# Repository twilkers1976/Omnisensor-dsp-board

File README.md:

# omnisensorv2
kicad 10.03 schematic and pcb project
#omni_cpu_board

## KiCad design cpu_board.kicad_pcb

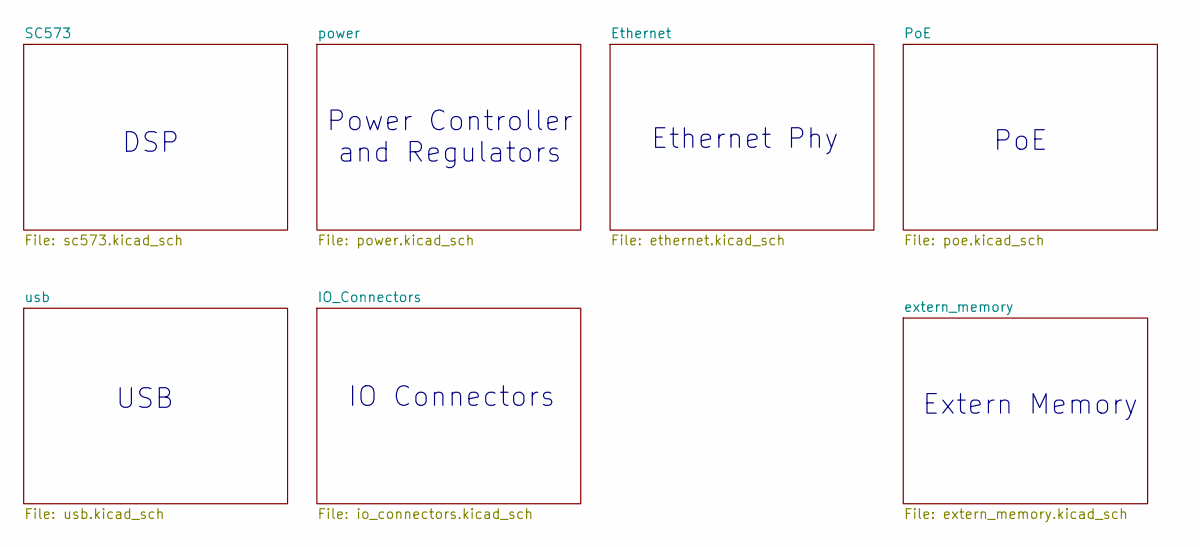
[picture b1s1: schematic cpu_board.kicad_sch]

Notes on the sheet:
PoE
Extern Memory
IO Connectors
Ethernet Phy
Power Controller and Regulators
DSP
USB

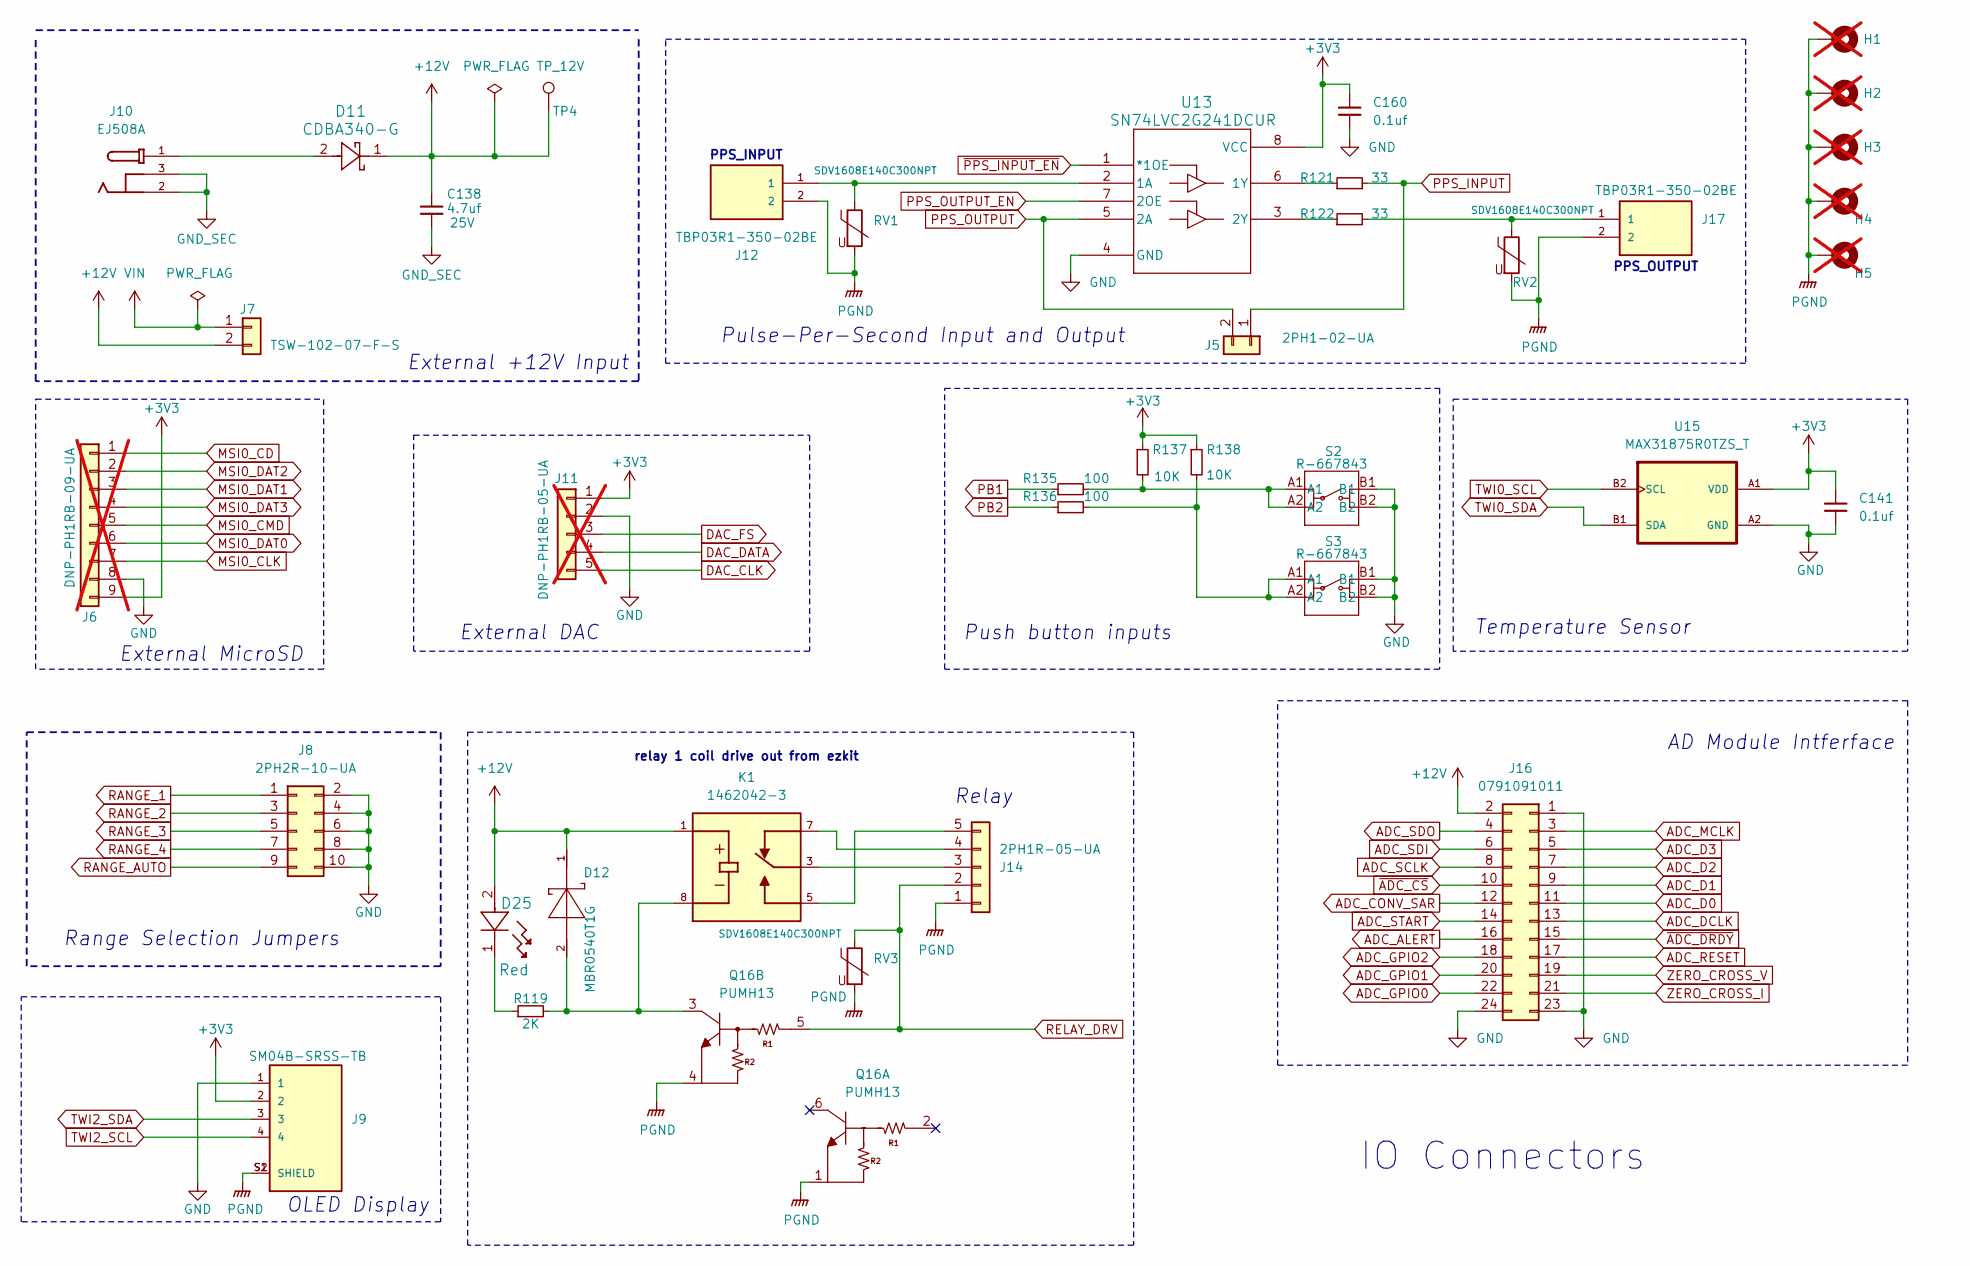
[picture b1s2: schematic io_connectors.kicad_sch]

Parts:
C138: 4.7uf; C_1210_3225Metric; Voltage 25V; Rating 25V; Part Number C1210C475K3RACTU
C141, C160: 0.1uf; C_0402_1005Metric; Rating 50V; Part Number 04025C104KAT2A
D11: CDBA340-G; CDBA-G; Part Number CDBA340-G
D12: MBR0540T1G; SOD-123; Part Number MBR0540T1G
D25: Red; LED_B1931NG_HVK; Part Number B1911USD-20D000114U1930
H1, H2, H3, H4, H5: MountingHole; MountingHole_2.5mm_Pad_TopBottom; not fitted
J5: 2PH1-02-UA; PinHeader_1x02_P2.00mm_Vertical; Part Number 2PH1-02-UA
J6: DNP-PH1RB-09-UA; PinHeader_1x09_P2.54mm_Vertical; Part Number PH1RB-09-UA; not fitted
J7: TSW-102-07-F-S; PinHeader_1x02_P2.54mm_Vertical; Rating 3A; Part Number TSW-102-07-F-S
J8: 2PH2R-10-UA; PinHeader_2x05_P2.00mm_Vertical; Part Number 2PH2R-10-UA
J9: SM04B-SRSS-TB; JST_SM04B-SRSS-TB(LF)(SN); Part Number SM04B-SRSS-TB
J10: EJ508A; MPD_EJ508A; PARTREV J
J11: DNP-PH1RB-05-UA; PinHeader_1x05_P2.54mm_Vertical; Part Number PH1RB-05-UA; not fitted
J12, J17: TBP03R1-350-02BE; CUI_TBP03R1-350-02BE; Part Number TBP03R1-350-02BE
J14: 2PH1R-05-UA; PinHeader_1x05_P2.00mm_Vertical; Part Number 2PH1R-05-UA
J16: 0791091011; PinSocket_2x12_P2.00mm_Vertical_SMD; Part Number 0791091011
K1: 1462042-3; PARTREV 0721
Q16: PUMH13; SOP65P210X110-6N; Part Numnber PUMH13F; DIGIKEY MUN5114T1GOSCT-ND
R119: 2K; R_0603_1608Metric; Rating 1/10 W; Part Number RN73H1JTTD2001F100
R121, R122: 33; R_0402_1005Metric; Part Number RMCF0402FT33R0
R135, R136: 100; R_0402_1005Metric; Part Number RMCF0402FT100R
R137, R138: 10K; R_0402_1005Metric; Part Number RMCF0402FT10K0
RV1, RV2, RV3: SDV1608E140C300NPT; R_0603_1608Metric; Part Number SDV1608E140C300NPT
S2, S3: R-667843; R-667843_MIT; PARTREV 14 Apr 22
TP4: TP_12V; TestPoint_Pad_D1.0mm
U13: SN74LVC2G241DCUR; DCU8; Part Number SN74LVC2G241DCUR
U15: MAX31875R0TZS_T; BGA4N40P2X2_83X83X37N; Part Number MAX31875R0TZS+T

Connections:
+3V3: C141.1, C160.1, J6.9, J9.2, J11.1, R137.1, R138.1, U13.8 (VCC), U15.A1 (VDD); also elsewhere on the board
+12V: C138.1, D11.1, D12.1, D25.2, J7.2, J16.2, K1.1, TP4.1 (1_1); also elsewhere on the board
ADC_ALERT: J16.16; also elsewhere on the board
ADC_CONV_SAR: J16.12; also elsewhere on the board
ADC_D0: J16.11; also elsewhere on the board
ADC_D1: J16.9; also elsewhere on the board
ADC_D2: J16.7; also elsewhere on the board
ADC_D3: J16.5; also elsewhere on the board
ADC_DCLK: J16.13; also elsewhere on the board
ADC_GPIO0: J16.22; also elsewhere on the board
ADC_GPIO1: J16.20; also elsewhere on the board
ADC_GPIO2: J16.18; also elsewhere on the board
ADC_MCLK: J16.3; also elsewhere on the board
ADC_RESET: J16.17; also elsewhere on the board
ADC_SCLK: J16.8; also elsewhere on the board
ADC_SDI: J16.6; also elsewhere on the board
ADC_SDO: J16.4; also elsewhere on the board
ADC_START: J16.14; also elsewhere on the board
DAC_CLK: J11.5; also elsewhere on the board
DAC_DATA: J11.4; also elsewhere on the board
DAC_FS: J11.3; also elsewhere on the board
GND: C141.2, C160.2, J6.8, J8.2, J8.4, J8.6, J8.8, J8.10, J9.1, J11.2, J16.1, J16.23, J16.24, S2.B1, S2.B2, S3.B1, S3.B2, U13.4 (GND), U15.A2 (GND); also elsewhere on the board
GND_SEC: C138.2, J10.2, J10.3; also elsewhere on the board
MSI0_CD: J6.1; also elsewhere on the board
MSI0_CLK: J6.7; also elsewhere on the board
MSI0_CMD: J6.5; also elsewhere on the board
MSI0_DAT0: J6.6; also elsewhere on the board
MSI0_DAT1: J6.3; also elsewhere on the board
MSI0_DAT2: J6.2; also elsewhere on the board
MSI0_DAT3: J6.4; also elsewhere on the board
unnamed: D11.2, J10.1
unnamed: D25.1, R119.1
unnamed: J14.3, K1.3
unnamed: J14.4, K1.7
unnamed: J14.5, K1.5
unnamed: J17.1, R122.2, RV2.1
unnamed: D12.2, K1.8, Q16.3 (COLLECTOR), R119.2
unnamed: R135.2, R137.2, S2.A1, S2.A2
unnamed: R136.2, R138.2, S3.A1, S3.A2
unnamed: J12.1, RV1.1, U13.2 (1A)
unnamed: R121.1, U13.6 (1Y)
unnamed: R122.1, U13.3 (2Y)
PB1: R135.1; also elsewhere on the board
PB2: R136.1; also elsewhere on the board
PGND: H1.1 (1_1), H2.1 (1_1), H3.1 (1_1), H4.1 (1_1), H5.1 (1_1), J9.S1 (SHIELD), J9.S2 (SHIELD), J12.2, J14.1, J17.2, Q16.1 (EMITTER), Q16.4 (EMITTER), RV1.2, RV2.2, RV3.2; also elsewhere on the board
PPS_INPUT: J5.1, R121.2; also elsewhere on the board
PPS_OUTPUT: J5.2, U13.5 (2A); also elsewhere on the board
PPS_OUTPUT_EN: U13.7 (2OE); also elsewhere on the board
RANGE_1: J8.1; also elsewhere on the board
RANGE_2: J8.3; also elsewhere on the board
RANGE_3: J8.5; also elsewhere on the board
RANGE_4: J8.7; also elsewhere on the board
RANGE_AUTO: J8.9; also elsewhere on the board
RELAY_DRV: J14.2, Q16.5 (BASE), RV3.1; also elsewhere on the board
TWI0_SCL: U15.B2 (SCL); also elsewhere on the board
TWI0_SDA: U15.B1 (SDA); also elsewhere on the board
TWI2_SCL: J9.4; also elsewhere on the board
TWI2_SDA: J9.3; also elsewhere on the board
VIN: J7.1; also elsewhere on the board
ZERO_CROSS_I: J16.21; also elsewhere on the board
ZERO_CROSS_V: J16.19; also elsewhere on the board
~ADC_CS: J16.10; also elsewhere on the board
~ADC_DRDY: J16.15; also elsewhere on the board
~PPS_INPUT_EN: U13.1 (*1OE); also elsewhere on the board

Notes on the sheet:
Range Selection Jumpers
relay 1 coil drive out from ezkit
External MicroSD
Push button inputs
IO Connectors
Pulse-Per-Second Input and Output
PPS_OUTPUT
PPS_INPUT
AD Module Intferface
External +12V Input
Temperature Sensor
OLED Display
Relay
External DAC

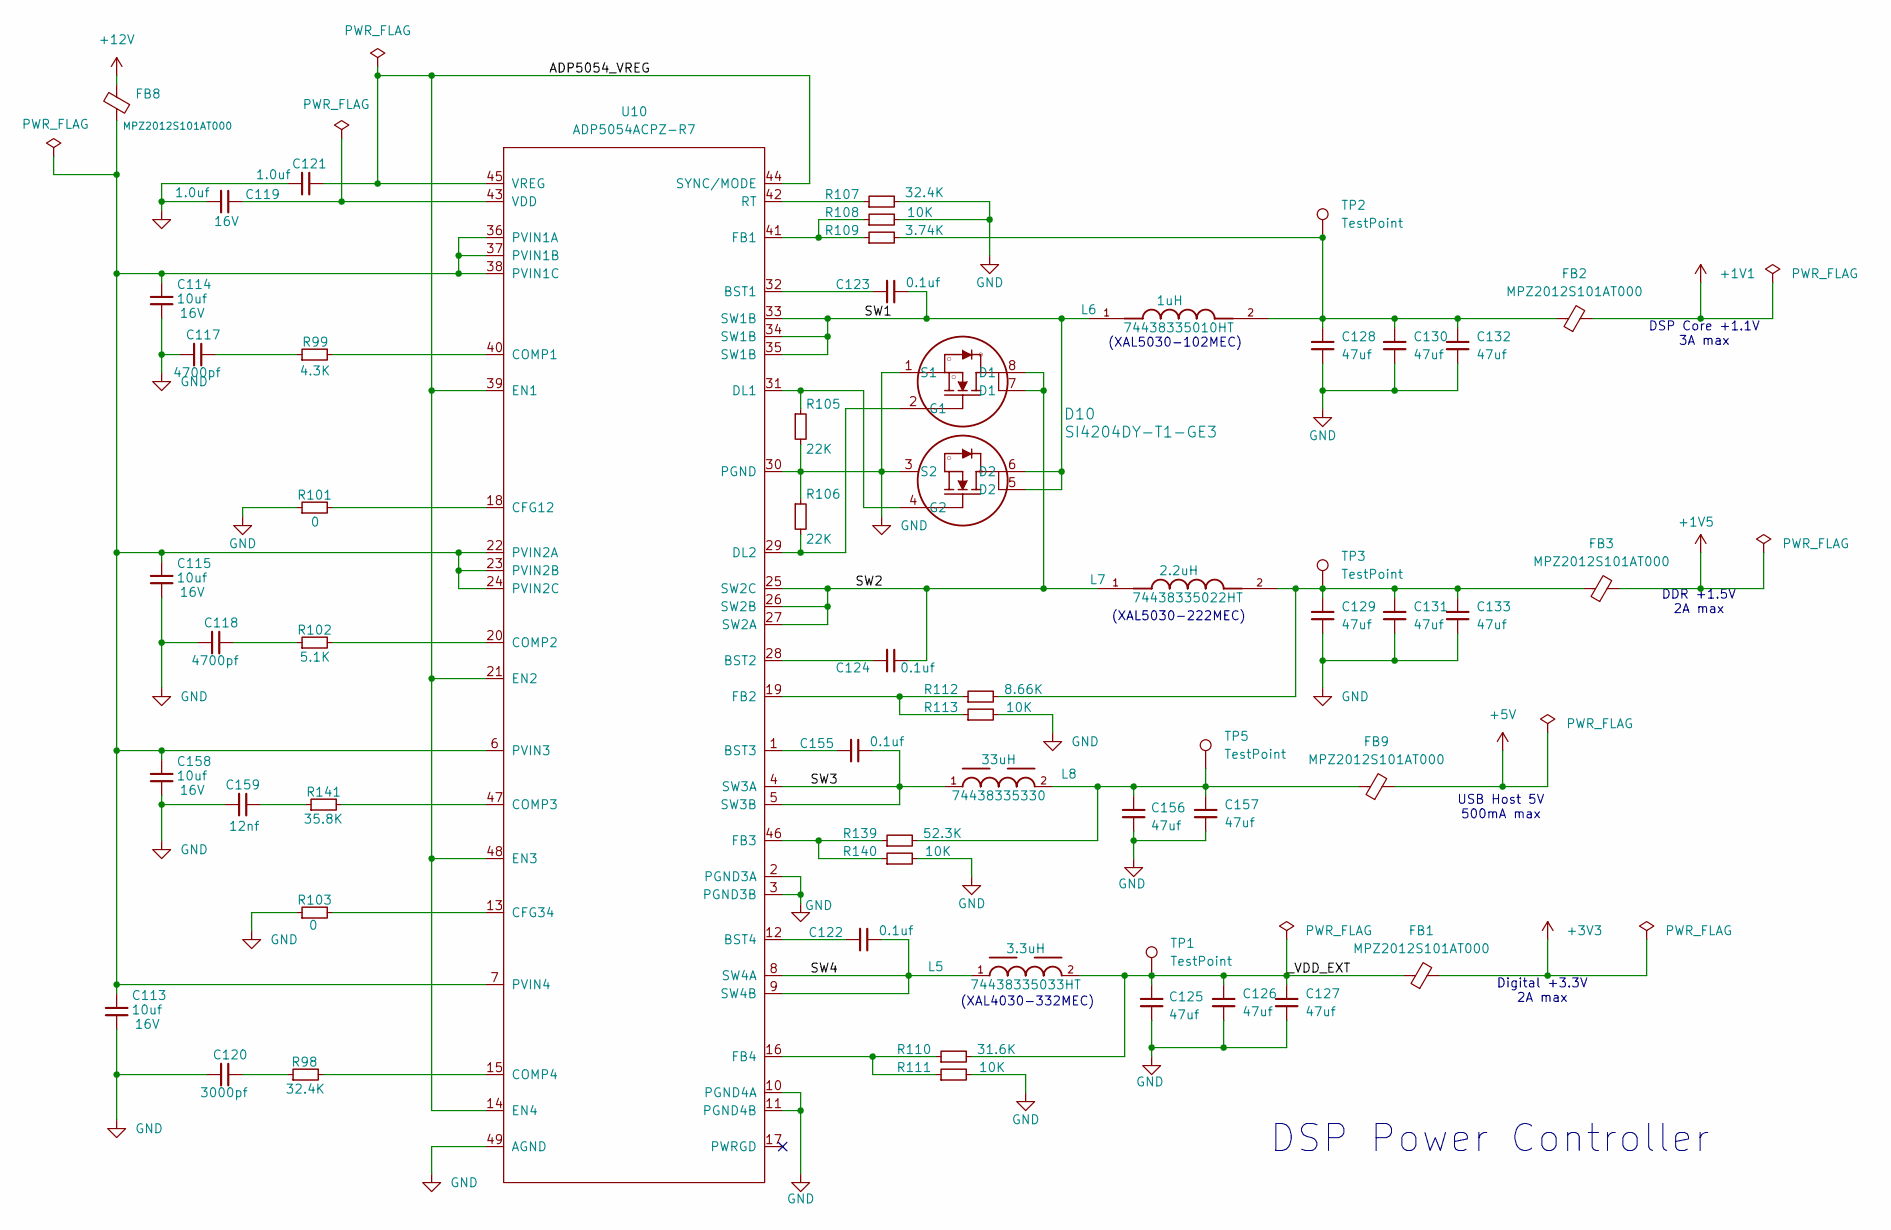
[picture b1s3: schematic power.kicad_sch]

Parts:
C113, C114, C115, C158: 10uf; C_0805_2012Metric; Voltage 16V; Rating 16V; Part Number EMK212BJ106KG-T
C117, C118: 4700pf; C_0402_1005Metric; Rating 50V; Part Number GCM155R71H472KA37D
C119, C121: 1.0uf; C_0402_1005Metric; Voltage 16V; Rating 16V; Part Number EMK105BJ105KV-F
C120: 3000pf; C_0402_1005Metric; Rating 50V; Part Number GMC04X7R302K50NT
C122, C123, C124, C155: 0.1uf; C_0402_1005Metric; Rating 50V; Part Number 04025C104KAT2A
C125, C126, C127, C128, C129, C130, C131, C132, C133, C156, C157: 47uf; C_0805_2012Metric; Rating 6.3V; Part Number JMK212BJ476MG-T
C159: 12nf; C_0402_1005Metric; Rating 50V; Part Number GCM155R71H122KA37D
D10: SI4204DY-T1-GE3; SOIC8_MS-012_VIS; Part Number SI4204DY-T1-GE3
FB1, FB3, FB8, FB9: MPZ2012S101AT000; L_0805_2012Metric; Rating 4A, 100 ohm; Part Number MPZ2012S101AT000
FB2: MPZ2012S101AT000; L_0805_2012Metric; Rating 4A, 100ohm; Part Number MPZ2012S101AT000
L5: 3.3uH; WE-MAPI_3015; Rating 2.7A; Part Number 74438335033HT
L6: 1uH; WE-MAPI_3015; Rating 4.5A; Part Number 74438335010HT
L7: 2.2uH; WE-MAPI_3015; Rating 3.2A; Part Number 74438335022HT
L8: 33uH; WE-MAPI_3015; Rating 500mA; Part Number 74438335330
R98, R107: 32.4K; R_0402_1005Metric; Part Number RMCF0402FT32K4
R99: 4.3K; R_0402_1005Metric; Part Number RMCF0402FT4K30
R101, R103: 0; R_0402_1005Metric; Part Number RMCF0402ZT0R00
R102: 5.1K; R_0402_1005Metric; Part Number RMCF0402FT5K10
R105, R106: 22K; R_0402_1005Metric; Part Number RMCF0402FT22K0
R108, R111, R113, R140: 10K; R_0402_1005Metric; Part Number RMCF0402FT10K0
R109: 3.74K; R_0402_1005Metric; Part Number RMCF0402FT3K74
R110: 31.6K; R_0402_1005Metric; Part Number RMCF0402FT31K6
R112: 8.66K; R_0402_1005Metric; Part Number RMCF0402FT8K66
R139: 52.3K; R_0402_1005Metric; Part Number RMCF0402FT52K3
R141: 35.8K; R_0402_1005Metric; Part Number RMCF0402FT35K7
TP1, TP2, TP3, TP5: TestPoint; TestPoint_Pad_D1.0mm
U10: ADP5054ACPZ-R7; CP_48_13_ADI; Part Number ADP5054ACPZ-R7

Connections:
+1V1: FB2.2; also elsewhere on the board
+1V5: FB3.2; also elsewhere on the board
+3V3: FB1.2; also elsewhere on the board
+5V: FB9.2; also elsewhere on the board
+12V: FB8.2; also elsewhere on the board
/power/ADP5054_VREG: C121.1, U10.14 (EN4), U10.21 (EN2), U10.39 (EN1), U10.44 (SYNC/MODE), U10.45 (VREG), U10.48 (EN3)
/power/SW1: C123.2, D10.5 (D2), D10.6 (D2), L6.1, U10.33 (SW1B), U10.34 (SW1B), U10.35 (SW1B)
/power/SW2: C124.2, D10.7 (D1), D10.8 (D1), L7.1, U10.25 (SW2C), U10.26 (SW2B), U10.27 (SW2A)
/power/SW3: C155.2, L8.1, U10.4 (SW3A), U10.5 (SW3B)
/power/SW4: C122.2, L5.1, U10.8 (SW4A), U10.9 (SW4B)
/power/_VDD_EXT: C125.1, C126.1, C127.1, FB1.1, L5.2, R110.2, TP1.1 (1_1)
GND: C113.2, C114.2, C115.2, C117.2, C118.2, C119.2, C120.2, C121.2, C125.2, C126.2, C127.2, C128.2, C129.2, C130.2, C131.2, C132.2, C133.2, C156.2, C157.2, C158.2, C159.2, D10.1 (S1), D10.3 (S2), R101.1, R103.1, R105.2, R106.1, R107.2, R108.2, R111.2, R113.2, R140.2, U10.2 (PGND3A), U10.3 (PGND3B), U10.10 (PGND4A), U10.11 (PGND4B), U10.30 (PGND), U10.49 (AGND); also elsewhere on the board
unnamed: C117.1, R99.1
unnamed: C118.1, R102.1
unnamed: C120.1, R98.1
unnamed: C128.1, C130.1, C132.1, FB2.1, L6.2, R109.2, TP2.1 (1_1)
unnamed: C129.1, C131.1, C133.1, FB3.1, L7.2, R112.2, TP3.1 (1_1)
unnamed: C156.1, C157.1, FB9.1, L8.2, R139.2, TP5.1 (1_1)
unnamed: C159.1, R141.1
unnamed: D10.2 (G1), R106.2, U10.29 (DL2)
unnamed: D10.4 (G2), R105.1, U10.31 (DL1)
unnamed: C123.1, U10.32 (BST1)
unnamed: C124.1, U10.28 (BST2)
unnamed: C155.1, U10.1 (BST3)
unnamed: C122.1, U10.12 (BST4)
unnamed: R101.2, U10.18 (CFG12)
unnamed: R103.2, U10.13 (CFG34)
unnamed: R99.2, U10.40 (COMP1)
unnamed: R102.2, U10.20 (COMP2)
unnamed: R141.2, U10.47 (COMP3)
unnamed: R98.2, U10.15 (COMP4)
unnamed: R108.1, R109.1, U10.41 (FB1)
unnamed: R112.1, R113.1, U10.19 (FB2)
unnamed: R139.1, R140.1, U10.46 (FB3)
unnamed: R110.1, R111.1, U10.16 (FB4)
unnamed: C113.1, C114.1, C115.1, C158.1, FB8.1, U10.6 (PVIN3), U10.7 (PVIN4), U10.22 (PVIN2A), U10.23 (PVIN2B), U10.24 (PVIN2C), U10.36 (PVIN1A), U10.37 (PVIN1B), U10.38 (PVIN1C)
unnamed: R107.1, U10.42 (RT)
unnamed: C119.1, U10.43 (VDD)

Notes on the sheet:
(XAL5030-222MEC)
(XAL5030-102MEC)
DDR +1.5V 2A max
Digital +3.3V 2A max
USB Host 5V 500mA max
DSP Core +1.1V 3A max
DSP Power Controller
(XAL4030-332MEC)

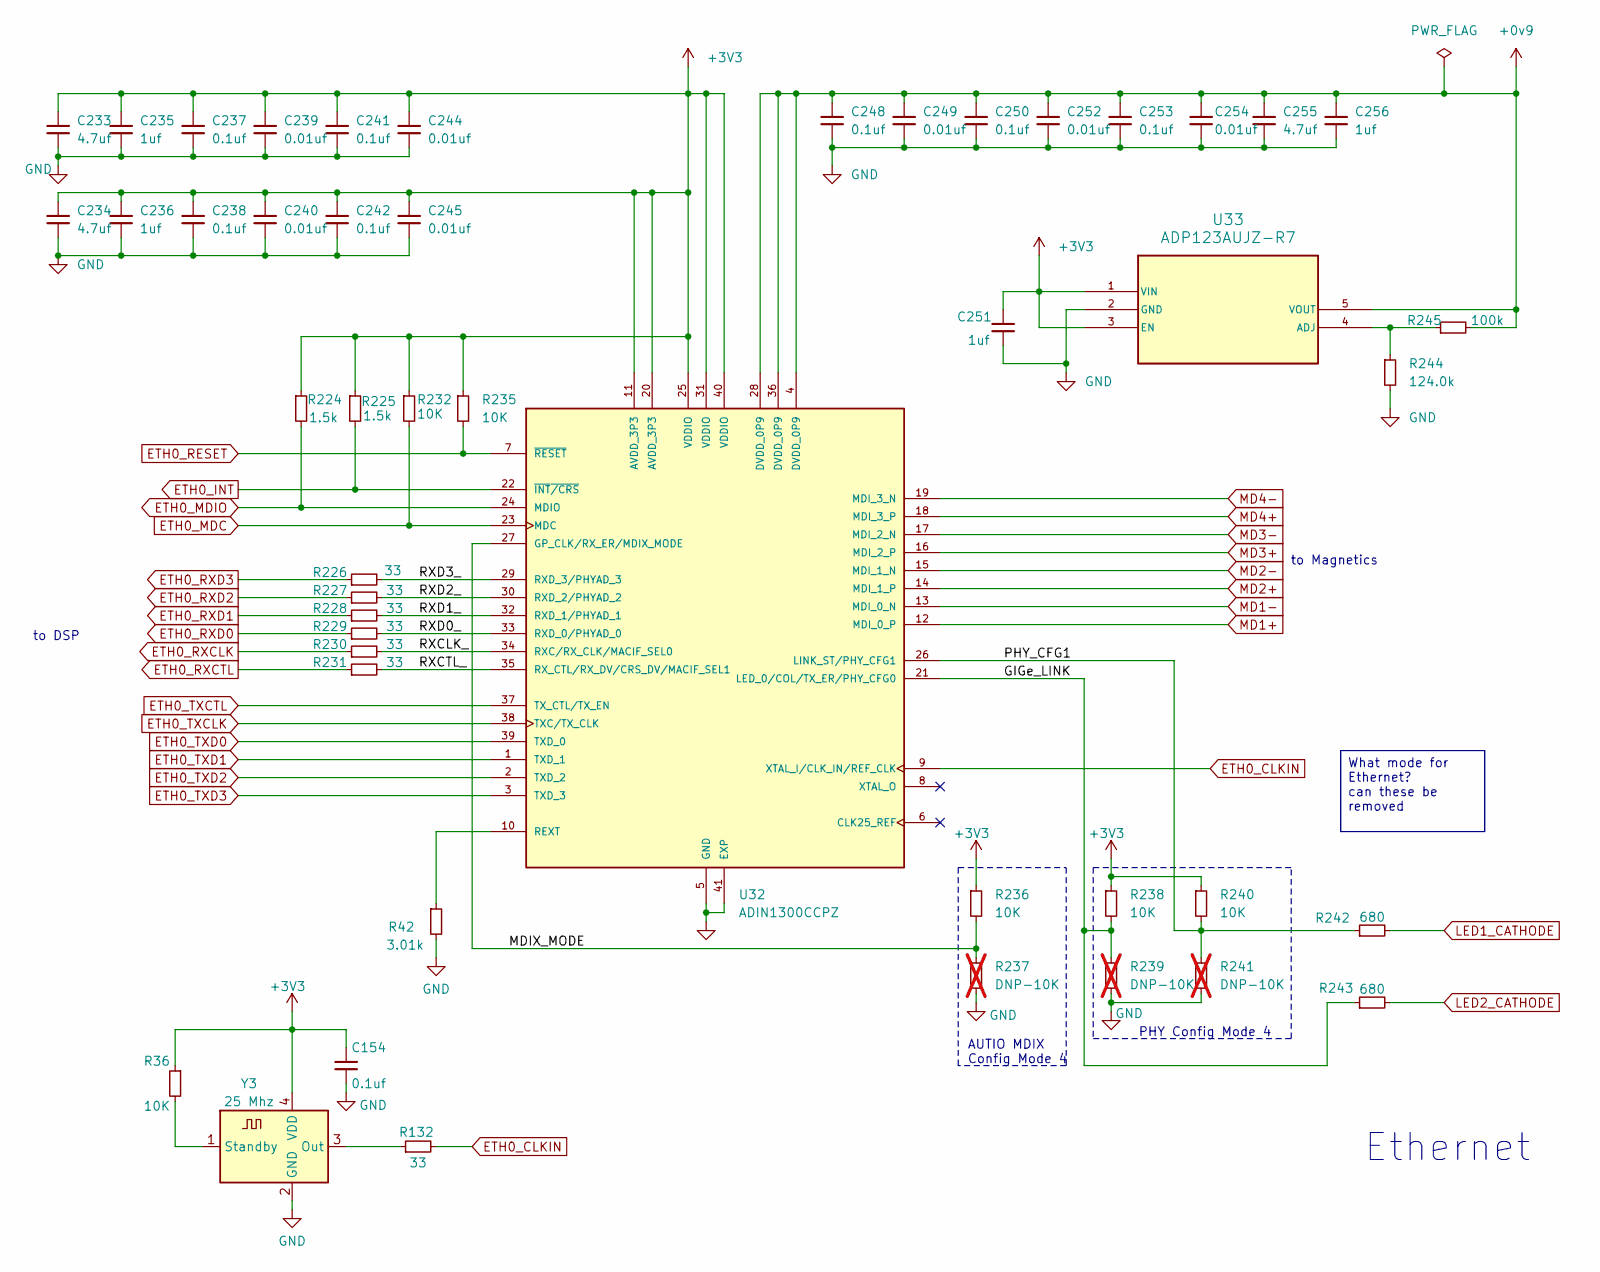
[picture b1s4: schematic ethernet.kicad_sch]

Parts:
C154, C237, C238, C241, C242, C248, C250, C253: 0.1uf; C_0402_1005Metric; Rating 50V; Part Number 04025C104KAT2A
C233, C234, C255: 4.7uf; C_0805_2012Metric; Rating 50V; Part Number CL21A475KBQNNNE
C235, C236, C251, C256: 1uf; C_0603_1608Metric; Rating 50V; Part Number 06035C105KAT2A
C239, C240, C244, C245, C249, C252, C254: 0.01uf; C_0402_1005Metric; Rating 50V; Part Number 04025C103KAT2A
R36, R232, R235, R236, R238, R240: 10K; R_0402_1005Metric; Part Number RMCF0402FT10K0
R42: 3.01k; R_0402_1005Metric; Part Number RMCF0402FT3K01
R132, R226, R227, R228, R229, R230, R231: 33; R_0402_1005Metric; Part Number RMCF0402FT33R0
R224, R225: 1.5k; R_0402_1005Metric; Part Number RMCF0402FT1K50
R237, R239, R241: DNP-10K; R_0402_1005Metric; Part Number RMCF0402FT10K0; not fitted
R242, R243: 680; R_0402_1005Metric; Part Number RMCF0402FT680R
R244: 124.0k; R_0402_1005Metric; Part Number RMCF0402FT124K
R245: 100k; R_0402_1005Metric; Part Number RMCF0402FT100K
U32: ADIN1300CCPZ; QFN50P600X600X80-41N; PARTREV 0
U33: ADP123AUJZ-R7; UJ-5_ADI; Part Number ADP123AUJZ-R7
Y3: 25 Mhz; OSC_4SMD_2.5MM_2.0MM; Part Number ECS-2520S33-250-FN-TR

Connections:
+0v9: C248.1, C249.1, C250.1, C252.1, C253.1, C254.1, C255.1, C256.1, R245.2, U32.4 (DVDD_0P9), U32.28 (DVDD_0P9), U32.36 (DVDD_0P9), U33.5 (VOUT)
+3V3: C154.1, C233.1, C234.1, C235.1, C236.1, C237.1, C238.1, C239.1, C240.1, C241.1, C242.1, C244.1, C245.1, C251.1, R36.1, R224.1, R225.1, R232.1, R235.1, R236.1, R238.1, R240.1, U32.11 (AVDD_3P3), U32.20 (AVDD_3P3), U32.25 (VDDIO), U32.31 (VDDIO), U32.40 (VDDIO), U33.1 (VIN), U33.3 (EN), Y3.4 (VDD); also elsewhere on the board
/Ethernet/GIGe_LINK: R238.2, R239.1, R243.1, U32.21 (LED_0/COL/TX_ER/PHY_CFG0)
/Ethernet/MDIX_MODE: R236.2, R237.1, U32.27 (GP_CLK/RX_ER/MDIX_MODE)
/Ethernet/PHY_CFG1: R240.2, R241.1, R242.1, U32.26 (LINK_ST/PHY_CFG1)
/Ethernet/RXCLK_: R230.2, U32.34 (RXC/RX_CLK/MACIF_SEL0)
/Ethernet/RXCTL_: R231.2, U32.35 (RX_CTL/RX_DV/CRS_DV/MACIF_SEL1)
/Ethernet/RXD0_: R229.2, U32.33 (RXD_0/PHYAD_0)
/Ethernet/RXD1_: R228.2, U32.32 (RXD_1/PHYAD_1)
/Ethernet/RXD2_: R227.2, U32.30 (RXD_2/PHYAD_2)
/Ethernet/RXD3_: R226.2, U32.29 (RXD_3/PHYAD_3)
ETH0_CLKIN: R132.2, U32.9 (XTAL_I/CLK_IN/REF_CLK); also elsewhere on the board
ETH0_INT: R225.2, U32.22 (~INT~/CRS); also elsewhere on the board
ETH0_MDC: R232.2, U32.23 (MDC); also elsewhere on the board
ETH0_MDIO: R224.2, U32.24 (MDIO); also elsewhere on the board
ETH0_RESET: R235.2, U32.7 (~RESET); also elsewhere on the board
ETH0_RXCLK: R230.1; also elsewhere on the board
ETH0_RXCTL: R231.1; also elsewhere on the board
ETH0_RXD0: R229.1; also elsewhere on the board
ETH0_RXD1: R228.1; also elsewhere on the board
ETH0_RXD2: R227.1; also elsewhere on the board
ETH0_RXD3: R226.1; also elsewhere on the board
ETH0_TXCLK: U32.38 (TXC/TX_CLK); also elsewhere on the board
ETH0_TXCTL: U32.37 (TX_CTL/TX_EN); also elsewhere on the board
ETH0_TXD0: U32.39 (TXD_0); also elsewhere on the board
ETH0_TXD1: U32.1 (TXD_1); also elsewhere on the board
ETH0_TXD2: U32.2 (TXD_2); also elsewhere on the board
ETH0_TXD3: U32.3 (TXD_3); also elsewhere on the board
GND: C154.2, C233.2, C234.2, C235.2, C236.2, C237.2, C238.2, C239.2, C240.2, C241.2, C242.2, C244.2, C245.2, C248.2, C249.2, C250.2, C251.2, C252.2, C253.2, C254.2, C255.2, C256.2, R42.2, R237.2, R239.2, R241.2, R244.2, U32.5 (GND), U32.41 (EXP), U33.2 (GND), Y3.2 (GND); also elsewhere on the board
LED1_CATHODE: R242.2; also elsewhere on the board
LED2_CATHODE: R243.2; also elsewhere on the board
MD1+: U32.12 (MDI_0_P); also elsewhere on the board
MD1-: U32.13 (MDI_0_N); also elsewhere on the board
MD2+: U32.14 (MDI_1_P); also elsewhere on the board
MD2-: U32.15 (MDI_1_N); also elsewhere on the board
MD3+: U32.16 (MDI_2_P); also elsewhere on the board
MD3-: U32.17 (MDI_2_N); also elsewhere on the board
MD4+: U32.18 (MDI_3_P); also elsewhere on the board
MD4-: U32.19 (MDI_3_N); also elsewhere on the board
unnamed: R42.1, U32.10 (REXT)
unnamed: R244.1, R245.1, U33.4 (ADJ)
unnamed: R132.1, Y3.3 (Out)
unnamed: R36.2, Y3.1 (Standby)

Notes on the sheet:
to Magnetics
to DSP
PHY Config Mode 4
Ethernet
AUTIO MDIX Config Mode 4
What mode for Ethernet? can these be removed

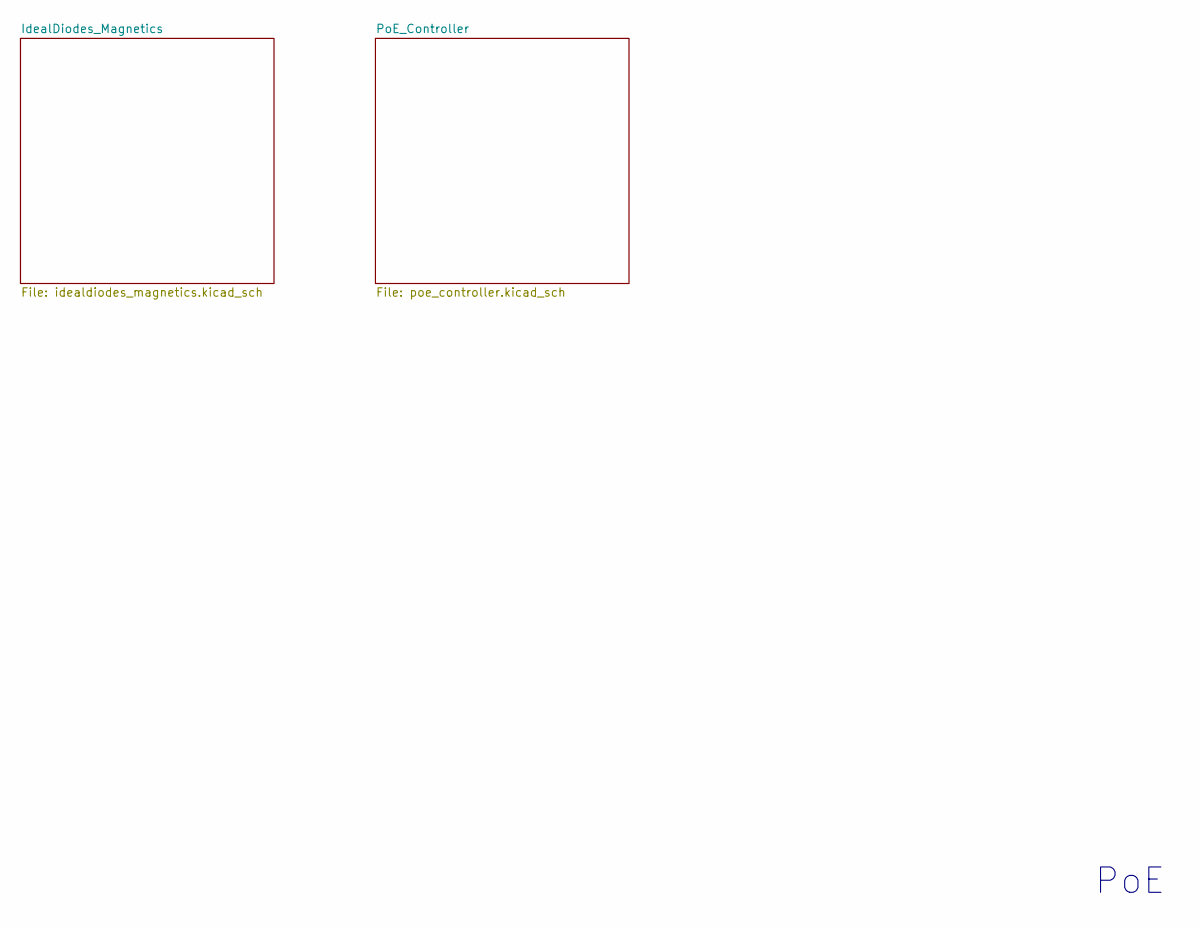
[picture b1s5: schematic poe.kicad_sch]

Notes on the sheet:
PoE

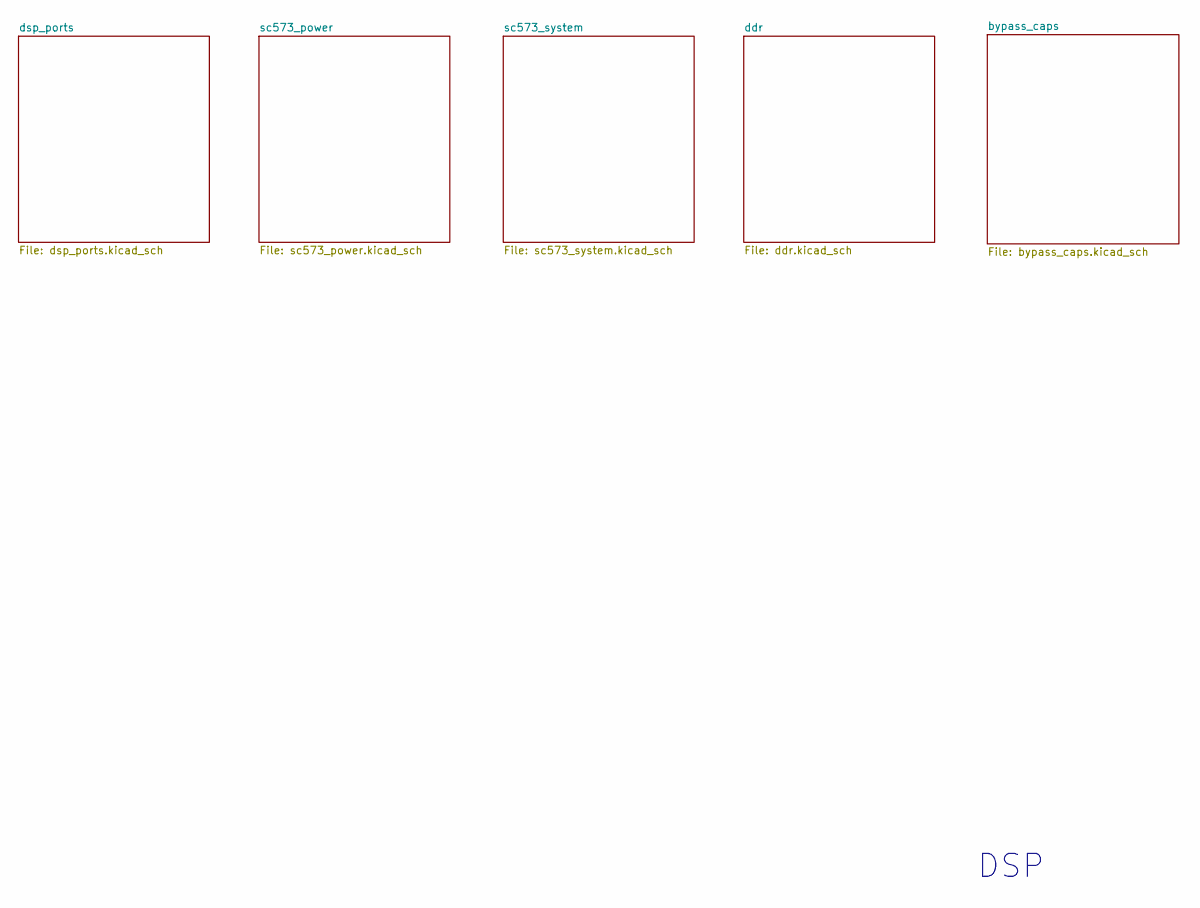
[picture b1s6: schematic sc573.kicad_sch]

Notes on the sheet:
DSP

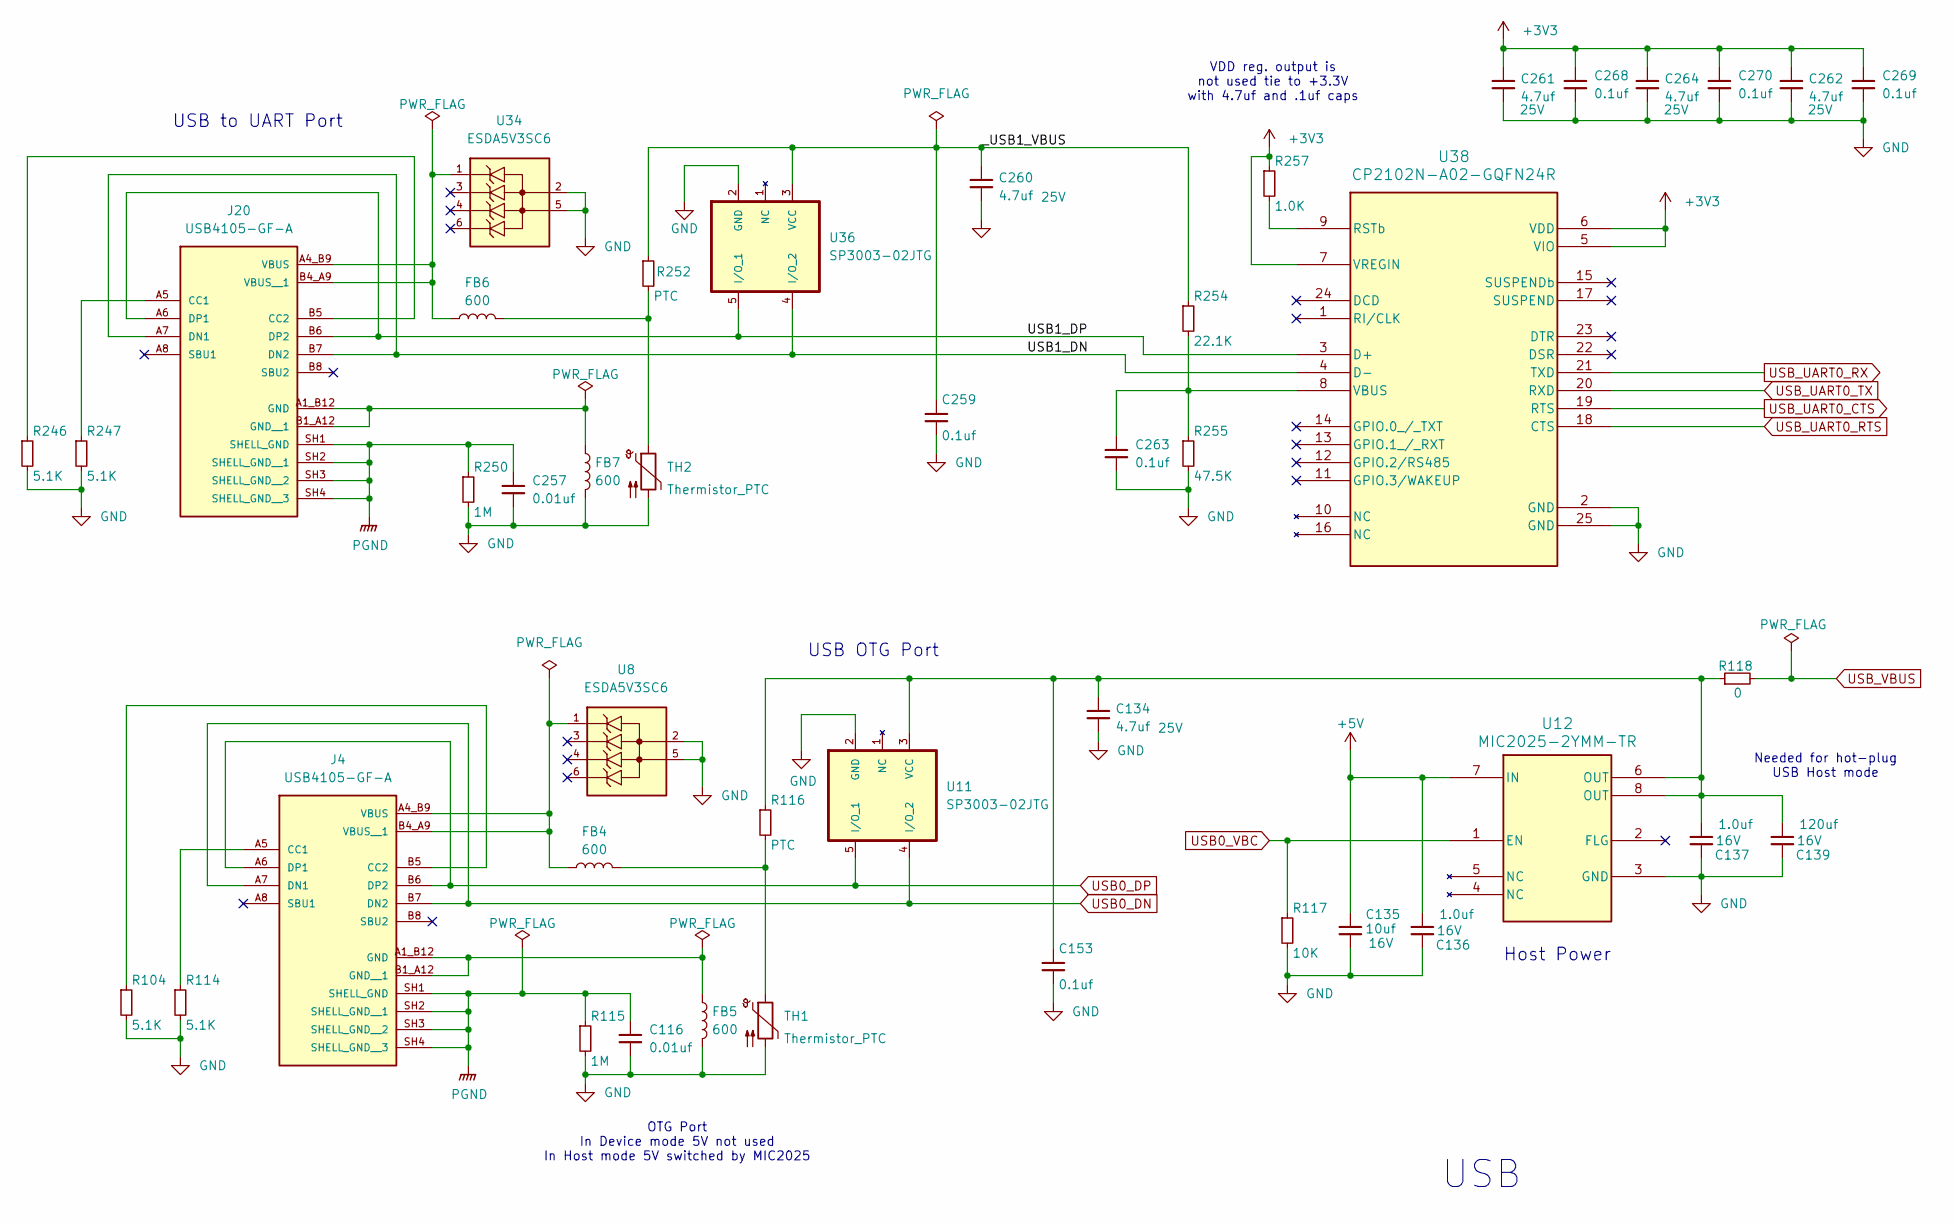
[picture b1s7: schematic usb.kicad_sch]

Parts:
C116, C257: 0.01uf; C_0402_1005Metric; Rating 50V; Part Number 04025C103KAT2A
C134, C260, C261, C262, C264: 4.7uf; C_0603_1608Metric; Rating 25V; Part Number CL10A475MA8NQNC
C135: 10uf; C_0805_2012Metric; Voltage 16V; Rating 16V; Part Number EMK212BJ106KG-T
C136, C137: 1.0uf; C_0402_1005Metric; Voltage 16V; Rating 16V; Part Number EMK105BJ105KV-F
C139: 120uf; CAP_X-7343-43_KEM; Voltage 16V; Rating 10V; Part Number A700X127M010ATE010
C153, C259, C263, C268, C269, C270: 0.1uf; C_0402_1005Metric; Rating 50V; Part Number 04025C104KAT2A
FB4, FB5, FB6, FB7: 600; L_0603_1608Metric_Pad1.05x0.95mm_HandSolder; Part Number 742863160
J4, J20: USB4105-GF-A; GCT_USB4105-GF-A; PARTREV B4
R104, R114, R246, R247: 5.1K; R_0402_1005Metric; Part Number RMCF0402FT5K10
R115, R250: 1M; R_0402_1005Metric; Part Number RMCF0402FT1M00
R116, R252: PTC; R_0603_1608Metric; Part Number 0603L050YR
R117: 10K; R_0402_1005Metric; Part Number RMCF0402FT10K0
R118: 0; R_0805_2012Metric; Part Number RMCF0805ZT0R00
R254: 22.1K; R_0402_1005Metric; Part Number RMCF0402FT22K1
R255: 47.5K; R_0402_1005Metric; Part Number RMCF0402FT47K5
R257: 1.0K; R_0402_1005Metric; Rating 1/16 W; Part Number RMCF0402FT1K00
TH1, TH2: Thermistor_PTC; R_0603_1608Metric_Pad0.98x0.95mm_HandSolder; Part Number V5.5MLA0603NH
U8, U34: ESDA5V3SC6; SOT23-6L; Part Number ESDA5V3SC6
U11, U36: SP3003-02JTG; SOT65P220X110-5N; MPN SP3003-02JTG
U12: MIC2025-2YMM-TR; MSOP-8_MM_MCH; Part Number MIC2025-2YMM-TR
U38: CP2102N-A02-GQFN24R; QFN24_SIL-M; Part Number CP2102N-A02-GQFN24R

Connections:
+3V3: C261.1, C262.1, C264.1, C268.1, C269.1, C270.1, R257.1, U38.5 (VIO), U38.6 (VDD), U38.7 (VREGIN); also elsewhere on the board
+5V: C135.1, C136.2, U12.7 (IN); also elsewhere on the board
/usb/USB1_DN: J20.A7 (DN1), J20.B7 (DN2), U36.4 (I/O_2), U38.4 (D-)
/usb/USB1_DP: J20.A6 (DP1), J20.B6 (DP2), U36.5 (I/O_1), U38.3 (D+)
/usb/_USB1_VBUS: C259.1, C260.1, R252.1, R254.1, U36.3 (VCC)
GND: C116.2, C134.2, C135.2, C136.1, C137.1, C139.1, C153.2, C257.2, C259.2, C260.2, C261.2, C262.2, C263.2, C264.2, C268.2, C269.2, C270.2, FB5.2, FB7.2, R104.2, R114.2, R115.2, R117.2, R246.2, R247.2, R250.2, R255.2, TH1.2, TH2.2, U8.2, U8.5, U11.2 (GND), U12.3 (GND), U34.2, U34.5, U36.2 (GND), U38.2 (GND), U38.25 (GND); also elsewhere on the board
unnamed: FB4.2, R116.2, TH1.1
unnamed: FB6.2, R252.2, TH2.1
unnamed: J4.A5 (CC1), R114.1
unnamed: J4.B5 (CC2), R104.1
unnamed: FB5.1, J4.A1_B12 (GND), J4.B1_A12 (GND__1)
unnamed: FB4.1, J4.A4_B9 (VBUS), J4.B4_A9 (VBUS__1), U8.1
unnamed: J20.A5 (CC1), R247.1
unnamed: J20.B5 (CC2), R246.1
unnamed: FB7.1, J20.A1_B12 (GND), J20.B1_A12 (GND__1)
unnamed: FB6.1, J20.A4_B9 (VBUS), J20.B4_A9 (VBUS__1), U34.1
unnamed: C134.1, C137.2, C139.2, C153.1, R116.1, R118.1, U11.3 (VCC), U12.6 (OUT), U12.8 (OUT)
unnamed: R257.2, U38.9 (RSTb)
unnamed: C263.1, R254.2, R255.1, U38.8 (VBUS)
PGND: C116.1, C257.1, J4.SH1 (SHELL_GND), J4.SH2 (SHELL_GND__1), J4.SH3 (SHELL_GND__2), J4.SH4 (SHELL_GND__3), J20.SH1 (SHELL_GND), J20.SH2 (SHELL_GND__1), J20.SH3 (SHELL_GND__2), J20.SH4 (SHELL_GND__3), R115.1, R250.1; also elsewhere on the board
USB0_DN: J4.A7 (DN1), J4.B7 (DN2), U11.4 (I/O_2); also elsewhere on the board
USB0_DP: J4.A6 (DP1), J4.B6 (DP2), U11.5 (I/O_1); also elsewhere on the board
USB0_VBC: R117.1, U12.1 (EN); also elsewhere on the board
USB_UART0_CTS: U38.19 (RTS); also elsewhere on the board
USB_UART0_RTS: U38.18 (CTS); also elsewhere on the board
USB_UART0_RX: U38.21 (TXD); also elsewhere on the board
USB_UART0_TX: U38.20 (RXD); also elsewhere on the board
USB_VBUS: R118.2; also elsewhere on the board

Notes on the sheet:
VDD reg. output is not used tie to +3.3V with 4.7uf and .1uf caps
USB OTG Port
USB to UART Port
Host Power
USB
OTG Port In Device mode 5V not used In Host mode 5V switched by MIC2025
Needed for hot-plug USB Host mode
